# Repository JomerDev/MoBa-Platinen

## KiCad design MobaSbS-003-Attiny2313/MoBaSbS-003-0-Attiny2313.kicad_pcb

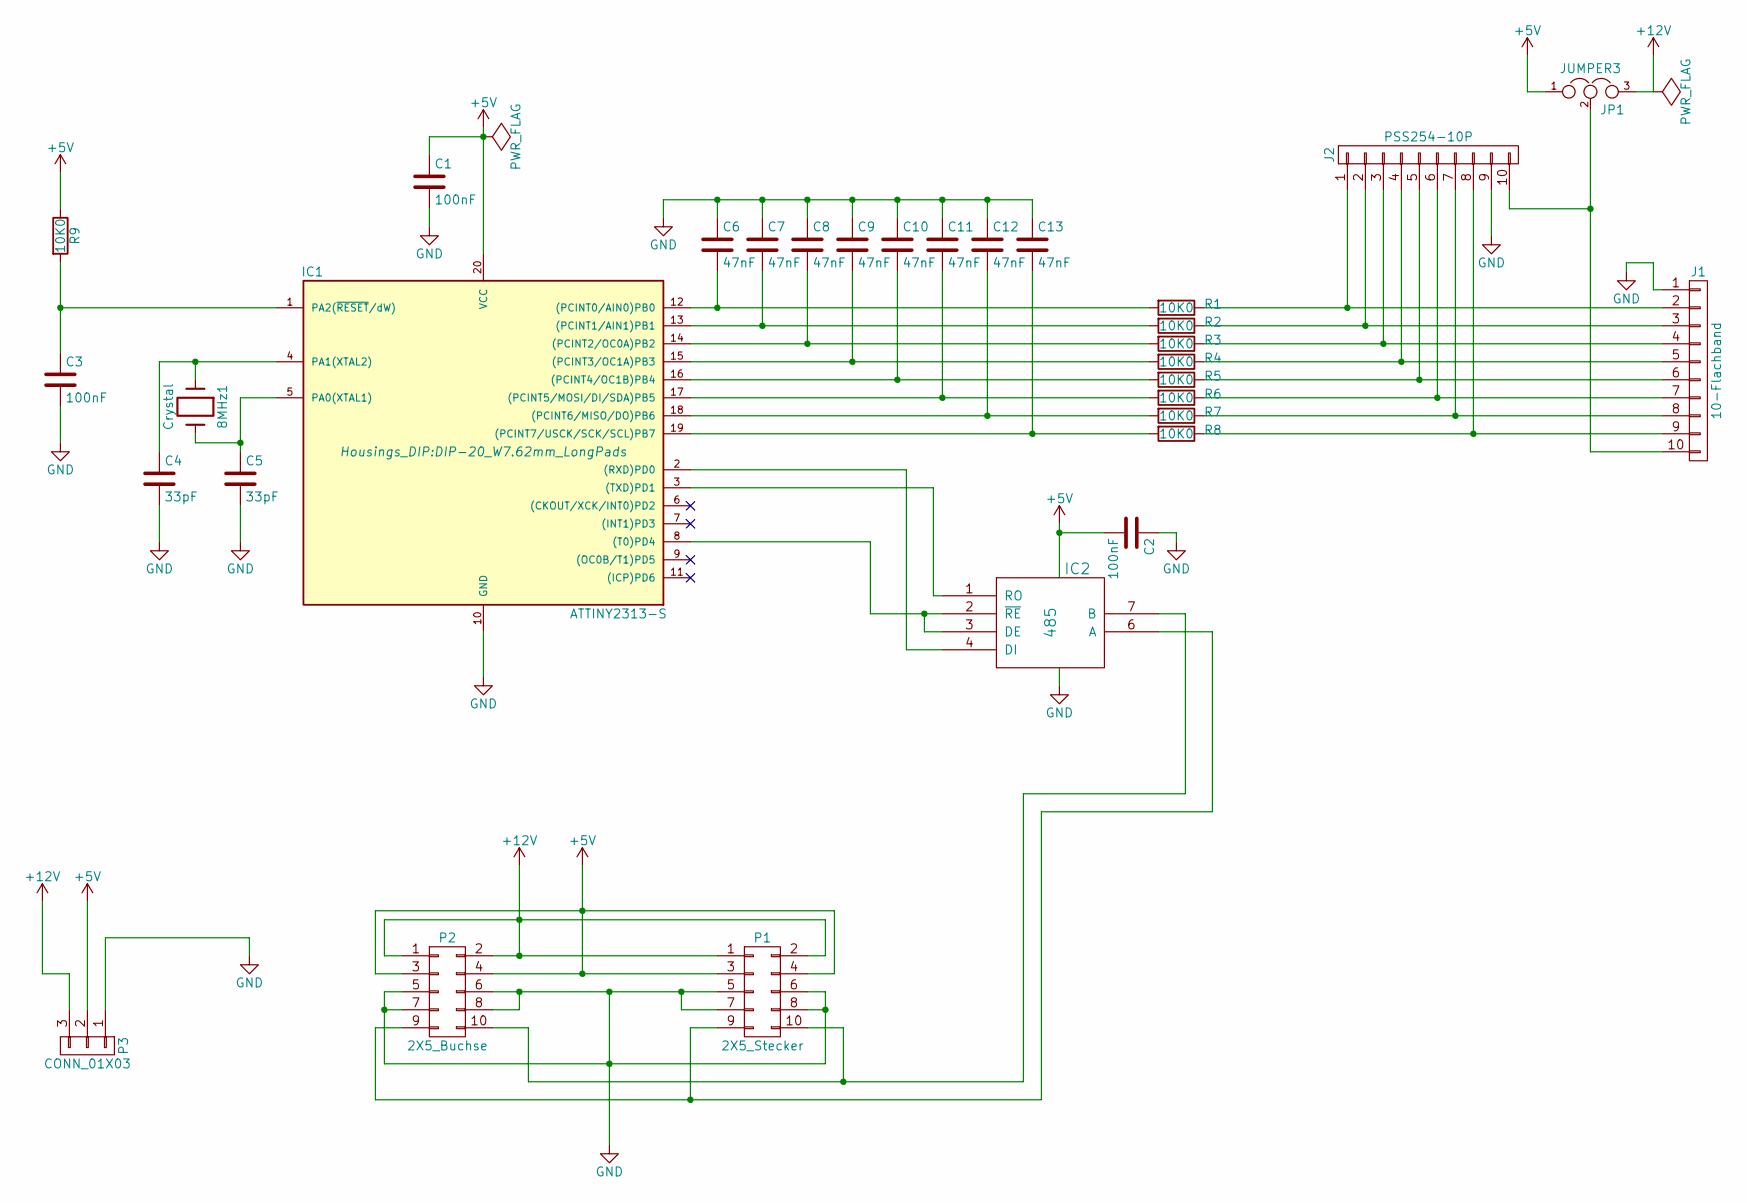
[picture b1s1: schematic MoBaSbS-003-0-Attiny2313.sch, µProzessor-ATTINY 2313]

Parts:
8MHz1: Crystal; Crystal_HC49-U_Vertical
C1, C2, C3: 100nF; C_1206
C4, C5: 33pF; C_1206
C6, C7, C8, C9, C10, C11, C12, C13: 47nF; C_1206
IC1: ATTINY2313-S; DIP-20_W7.62mm_LongPads
IC2: 485; DIP-8_W7.62mm_LongPads
J1: 10-Flachband; IDC_Header_Straight_10pins
J2: PSS254-10P; PSS254-10G
JP1: JUMPER3; Socket_Strip_Straight_1x03
P1: 2X5_Stecker; Pin_Header_Angled_2x05
P2: 2X5_Buchse; Socket_Strip_Angled_2x05
P3: CONN_01X03; PSS254-3G
R1, R2, R3, R4, R5, R6, R7, R8, R9: 10K0; R_1206

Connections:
+5V: C1.1, C2.2, IC1.20 (VCC), IC2.8 (VCC), JP1.1, P1.3, P1.4, P2.3, P2.4, P3.2, R9.1
+12V: JP1.3, P1.1, P1.2, P2.1, P2.2, P3.3
GND: C1.2, C2.1, C3.2, C4.2, C5.2, C6.1, C7.1, C8.1, C9.1, C10.1, C11.1, C12.1, C13.1, IC1.10 (GND), IC2.5 (GND), J1.1, J2.9, P1.5, P1.6, P1.7, P1.8, P2.5, P2.6, P2.7, P2.8, P3.1
unnamed 3: 8MHz1.1, C4.1, IC1.4 (PA1(XTAL2)); also elsewhere on the board
unnamed 4: 8MHz1.2, C5.1, IC1.5 (PA0(XTAL1)); also elsewhere on the board
unnamed: C3.1, IC1.1 (PA2(~RESET~/dW)), R9.2
unnamed: C6.2, IC1.12 ((PCINT0/AIN0)PB0), R1.2
unnamed: C7.2, IC1.13 ((PCINT1/AIN1)PB1), R2.2
unnamed: C8.2, IC1.14 ((PCINT2/OC0A)PB2), R3.2
unnamed: C9.2, IC1.15 ((PCINT3/OC1A)PB3), R4.2
unnamed: C10.2, IC1.16 ((PCINT4/OC1B)PB4), R5.2
unnamed: C11.2, IC1.17 ((PCINT5/MOSI/DI/SDA)PB5), R6.2
unnamed: C12.2, IC1.18 ((PCINT6/MISO/DO)PB6), R7.2
unnamed: C13.2, IC1.19 ((PCINT7/USCK/SCK/SCL)PB7), R8.2
unnamed: IC1.2 ((RXD)PD0), IC2.4 (DI)
unnamed: IC1.3 ((TXD)PD1), IC2.1 (RO)
unnamed: IC1.8 ((T0)PD4), IC2.2 (~RE), IC2.3 (DE)
unnamed: IC2.6 (A), P1.9, P2.9
unnamed: IC2.7 (B), P1.10, P2.10
unnamed: J1.2, J2.1, R1.1
unnamed: J1.3, J2.2, R2.1
unnamed: J1.4, J2.3, R3.1
unnamed: J1.5, J2.4, R4.1
unnamed: J1.6, J2.5, R5.1
unnamed: J1.7, J2.6, R6.1
unnamed: J1.8, J2.7, R7.1
unnamed: J1.9, J2.8, R8.1
unnamed: J1.10, J2.10, JP1.2

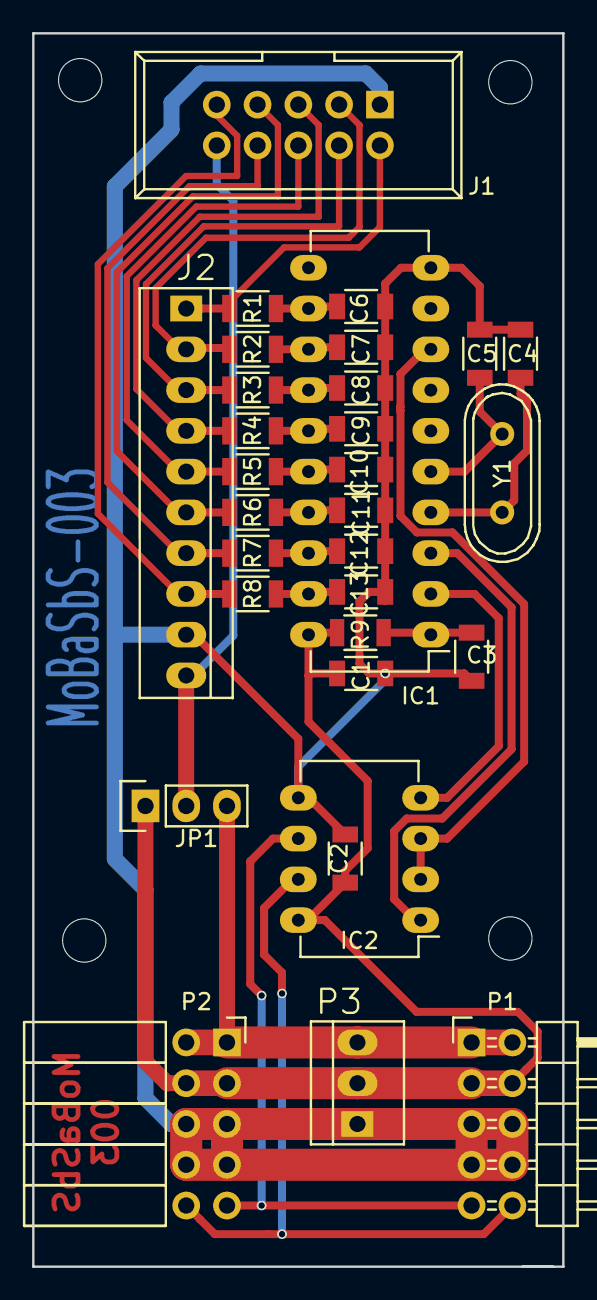
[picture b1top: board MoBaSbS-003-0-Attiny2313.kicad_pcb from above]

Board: 2 copper layers, 33.0 x 76.8 mm, 31 parts (0 on the bottom side), 28 nets.

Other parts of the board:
Y1: 8MHz; Crystal_HC49-U_Vertical

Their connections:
unnamed 3: Y1.1; also elsewhere on the board
unnamed 4: Y1.2; also elsewhere on the board
